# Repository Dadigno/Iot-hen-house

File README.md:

# Iot Hen House
This piece of elettronic gives smart properties to my hen house. It allows you to control a DC motor through WiFi (esp-12e) that opens and closes the door of the chicken coop.

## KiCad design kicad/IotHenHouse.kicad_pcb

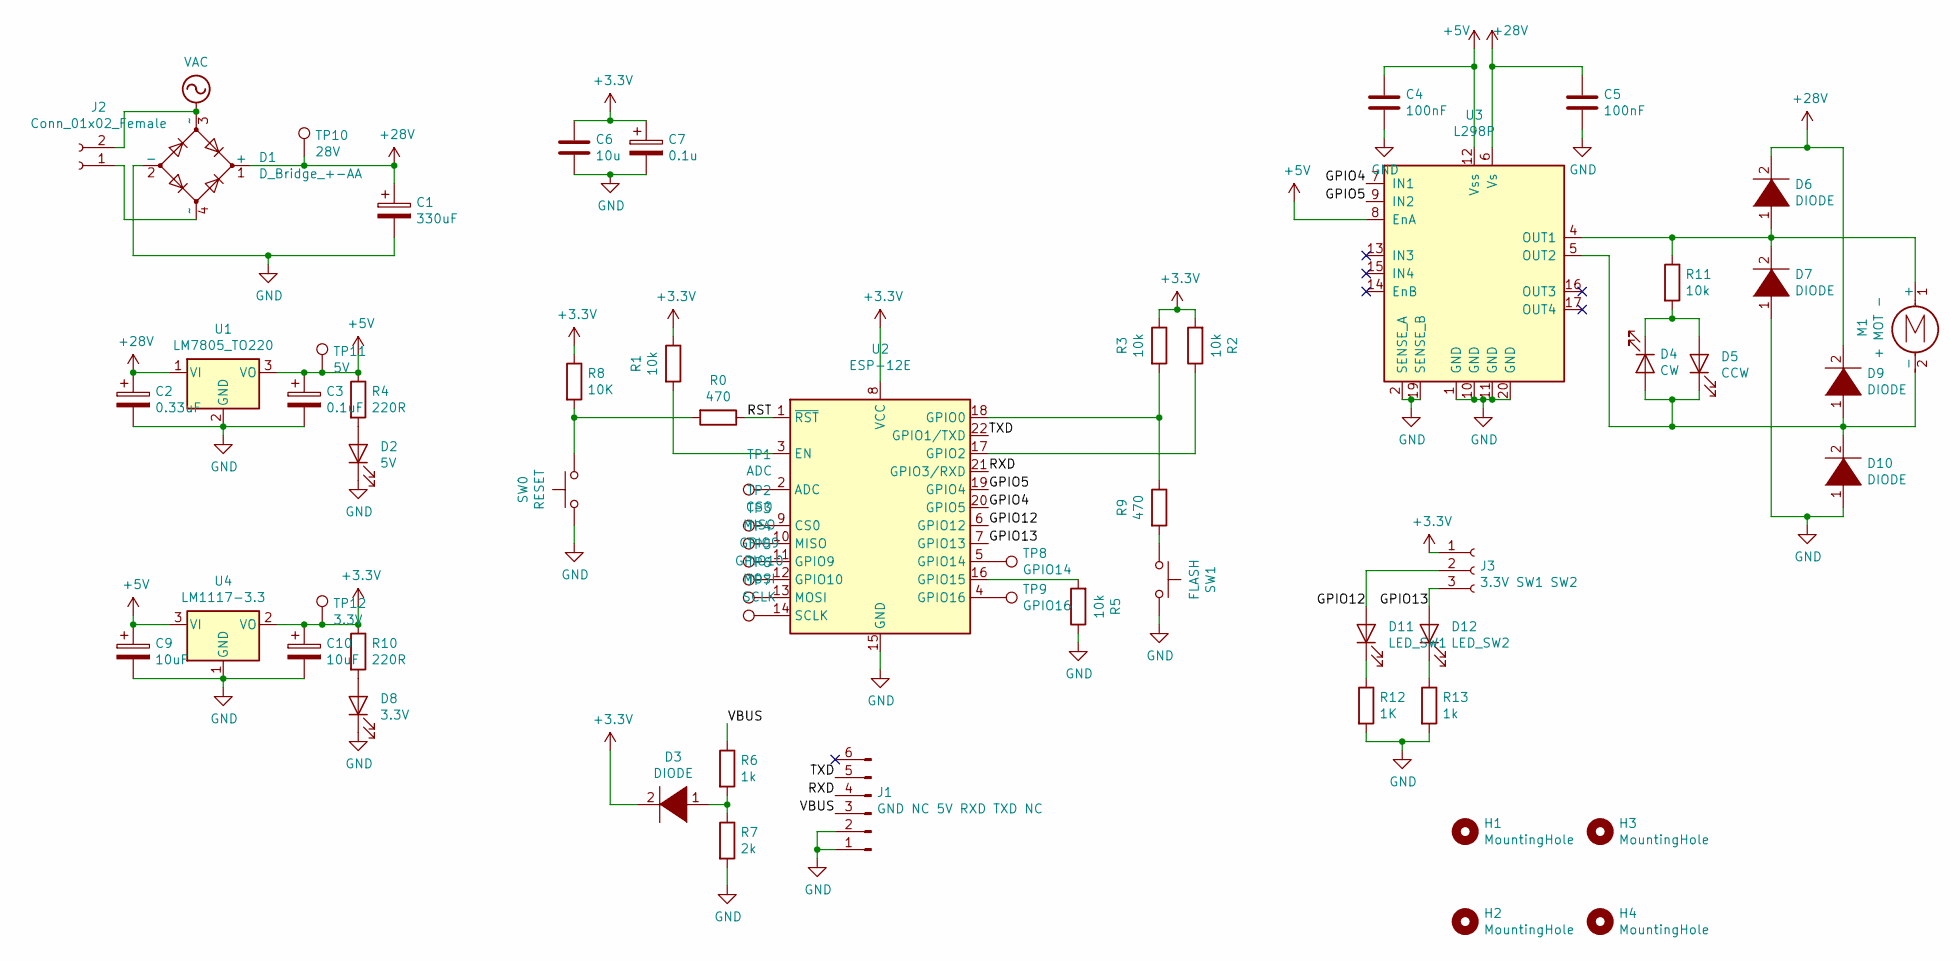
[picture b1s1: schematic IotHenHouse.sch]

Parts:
C1: 330uF; CP_Radial_D8.0mm_P2.50mm
C2: 0.33uF; CP_Radial_D8.0mm_P3.50mm
C3: 0.1uF; CP_Radial_D8.0mm_P3.50mm
C4, C5: 100nF; CP_Elec_4x4.5
C6: 10u; C_1210_3225Metric_Pad1.42x2.65mm_HandSolder
C7: 0.1u; C_1210_3225Metric_Pad1.42x2.65mm_HandSolder
C9, C10: 10uF; C_1210_3225Metric_Pad1.42x2.65mm_HandSolder
D1: D_Bridge_+-AA; Diode_Bridge_32.0x5.6x17.0mm_P10.0mm_P7.5mm
D2: 5V; LED_0805_2012Metric_Pad1.15x1.40mm_HandSolder
D3, D6, D7, D9, D10: DIODE; D_SMA
D4: CW; LED_0805_2012Metric_Pad1.15x1.40mm_HandSolder
D5: CCW; LED_0805_2012Metric_Pad1.15x1.40mm_HandSolder
D8: 3.3V; LED_0805_2012Metric_Pad1.15x1.40mm_HandSolder
D11: LED_SW1; LED_0805_2012Metric_Pad1.15x1.40mm_HandSolder
D12: LED_SW2; LED_0805_2012Metric_Pad1.15x1.40mm_HandSolder
H1, H2, H3, H4: MountingHole; MountingHole_3.2mm_M3_Pad_Via
J1: GND NC 5V RXD TXD NC; PinHeader_1x06_P2.54mm_Vertical
J2: Conn_01x02_Female; PinHeader_1x02_P2.54mm_Vertical
J3: 3.3V SW1 SW2; JST_NV_B03P-NV_1x03_P5.00mm_Vertical
M1: + MOT -; JST_NV_B02P-NV_1x02_P5.00mm_Vertical
R0, R9: 470; R_0805_2012Metric_Pad1.15x1.40mm_HandSolder
R1, R2, R3, R5, R11: 10k; R_0805_2012Metric_Pad1.15x1.40mm_HandSolder
R4, R10: 220R; R_0805_2012Metric_Pad1.15x1.40mm_HandSolder
R6, R13: 1k; R_0805_2012Metric_Pad1.15x1.40mm_HandSolder
R7: 2k; R_0805_2012Metric_Pad1.15x1.40mm_HandSolder
R8: 10K; R_0805_2012Metric_Pad1.15x1.40mm_HandSolder
R12: 1K; R_0805_2012Metric_Pad1.15x1.40mm_HandSolder
SW0: RESET; SW_SPST_CK_RS282G05A3
SW1: FLASH; PinHeader_1x02_P2.54mm_Vertical
TP1: ADC; TestPoint_Pad_D1.5mm
TP2: CSO; TestPoint_Pad_D1.5mm
TP3: MISO; TestPoint_Pad_D1.5mm
TP4: GPIO9; TestPoint_Pad_D1.5mm
TP5: GPIO10; TestPoint_Pad_D1.5mm
TP6: MOSI; TestPoint_Pad_D1.5mm
TP7: SCLK; TestPoint_Pad_D1.5mm
TP8: GPIO14; TestPoint_Pad_D1.5mm
TP9: GPIO16; TestPoint_Pad_D1.5mm
TP10: 28V; TestPoint_Pad_D1.5mm
TP11: 5V; TestPoint_Pad_D1.5mm
TP12: 3.3V; TestPoint_Pad_D1.5mm
U1: LM7805_TO220; TO-220-3_Vertical
U2: ESP-12E
U3: L298P; PowerSO-20
U4: LM1117-3.3; SOT-223

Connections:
+3V3: C6.1, C7.1, C10.1, D3.2 (A), J3.1, R1.1, R2.2, R3.1, R8.1, R10.1, TP12.1, U2.8 (VCC), U4.2 (VO)
+5V: C3.1, C4.1, C9.1, R4.1, TP11.1, U1.3 (VO), U3.8 (EnA), U3.12 (Vss), U4.3 (VI)
+28V: C1.1, C2.1, C5.1, D1.1 (+), D6.2 (A), D9.2 (A), TP10.1, U1.1 (VI), U3.6 (Vs)
/GPIO4: U2.20 (GPIO5), U3.7 (IN1)
/GPIO5: U2.19 (GPIO4), U3.9 (IN2)
/GPIO12: D11.2 (A), J3.2, U2.6 (GPIO12)
/GPIO13: D12.2 (A), J3.3, U2.7 (GPIO13)
/RST: R0.1, U2.1 (~RST)
/RXD: J1.4, U2.21 (GPIO3/RXD)
/TXD: J1.5, U2.22 (GPIO1/TXD)
/VBUS: J1.3, R6.1
GND: C1.2, C2.2, C3.2, C4.2, C5.2, C6.2, C7.2, C9.2, C10.2, D1.2 (-), D2.1 (K), D7.1 (K), D8.1 (K), D10.1 (K), J1.1, J1.2, R5.1, R7.2, R12.2, R13.2, SW0.1, SW1.2, U1.2 (GND), U2.15 (GND), U3.1 (GND), U3.2 (SENSE_A), U3.10 (GND), U3.11 (GND), U3.19 (SENSE_B), U3.20 (GND), U4.1 (GND)
unnamed 12: D1.4 (~~), J2.1; also elsewhere on the board
unnamed: D2.2 (A), R4.2
unnamed: D3.1 (K), R6.2, R7.1
unnamed: D4.1 (K), D5.2 (A), R11.2
unnamed: D6.1 (K), D7.2 (A), M1.1 (+), R11.1, U3.4 (OUT1)
unnamed: D8.2 (A), R10.2
unnamed: D4.2 (A), D5.1 (K), D9.1 (K), D10.2 (A), M1.2 (-), U3.5 (OUT2)
unnamed: D11.1 (K), R12.1
unnamed: D12.1 (K), R13.1
unnamed: R0.2, R8.2, SW0.2
unnamed: R1.2, U2.3 (EN)
unnamed: R2.1, U2.17 (GPIO2)
unnamed: R3.2, R9.1, U2.18 (GPIO0)
unnamed: R5.2, U2.16 (GPIO15)
unnamed: R9.2, SW1.1
unnamed: TP1.1, U2.2 (ADC)
unnamed: TP2.1, U2.9 (CS0)
unnamed: TP3.1, U2.10 (MISO)
unnamed: TP4.1, U2.11 (GPIO9)
unnamed: TP5.1, U2.12 (GPIO10)
unnamed: TP6.1, U2.13 (MOSI)
unnamed: TP7.1, U2.14 (SCLK)
unnamed: TP8.1, U2.5 (GPIO14)
unnamed: TP9.1, U2.4 (GPIO16)
VAC: D1.3 (~~), J2.2; also elsewhere on the board

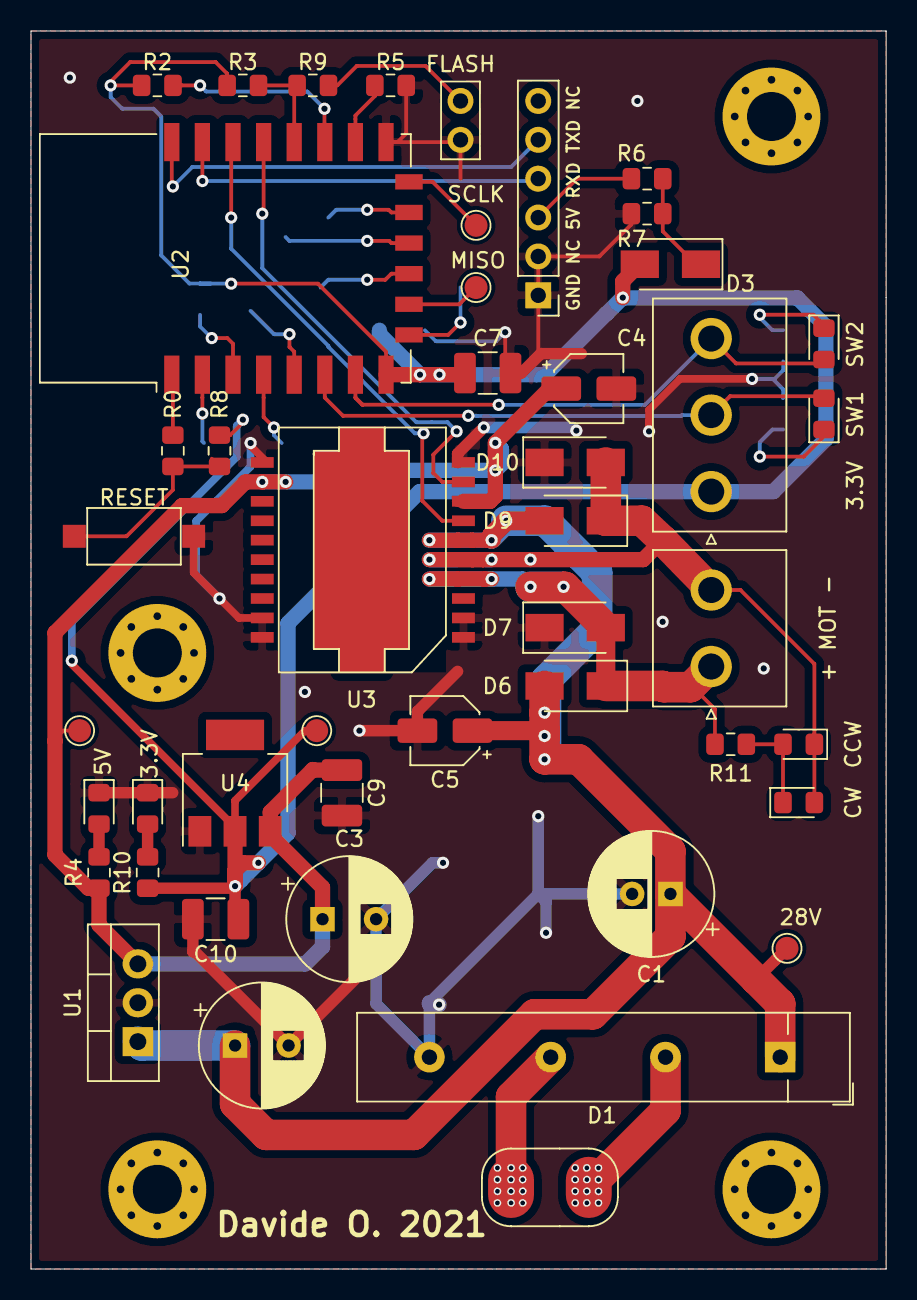
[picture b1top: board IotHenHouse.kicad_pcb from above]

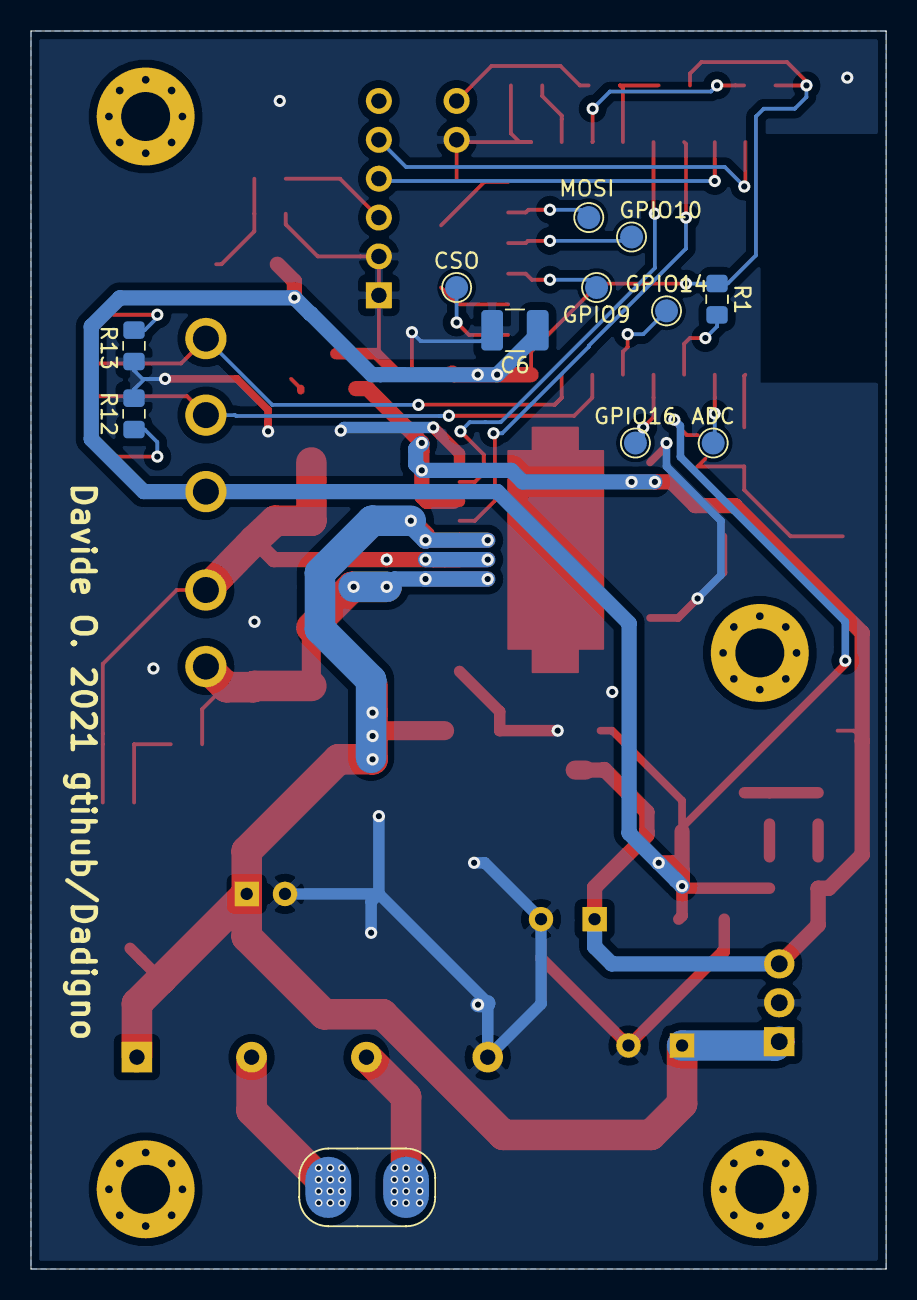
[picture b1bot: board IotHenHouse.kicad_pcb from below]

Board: 2 copper layers, 55.9 x 80.9 mm, 62 parts (12 on the bottom side), 37 nets.

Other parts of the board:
J2#2: Conn_01x02_Female; PinHeader_1x02_P2.54mm_Vertical

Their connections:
unnamed 12: J2#2.1; also elsewhere on the board
VAC: J2#2.2; also elsewhere on the board

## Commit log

2021-02-28 Kicad Project
2021-02-28 add gerbers and datasheets
2021-02-28 add media
2021-03-05 gitignore updated
2021-03-05 deleted
2021-03-05 gitignore pio add
2021-03-05 updated pio gitignore
2021-03-05 platformio project created
2021-03-05 semilimes library added
2021-03-05 new kicad directory
2021-03-05 fixed readme
2021-03-05 first connection test code
2021-03-05 fixed /iot_han_house/include/.gitignore
2021-03-05 new libraries added
2021-03-05 renamed directory
2021-03-08 new library added
2021-03-08 some changes to the libraries, tested on esp8266: receive correctly but send nothing
2021-03-08 new semilimes libraries and bugs fixed
2021-03-25 update firmware
2021-04-28 mounting holes
2021-04-28 logos
2021-08-07 last commit for version 1.0
